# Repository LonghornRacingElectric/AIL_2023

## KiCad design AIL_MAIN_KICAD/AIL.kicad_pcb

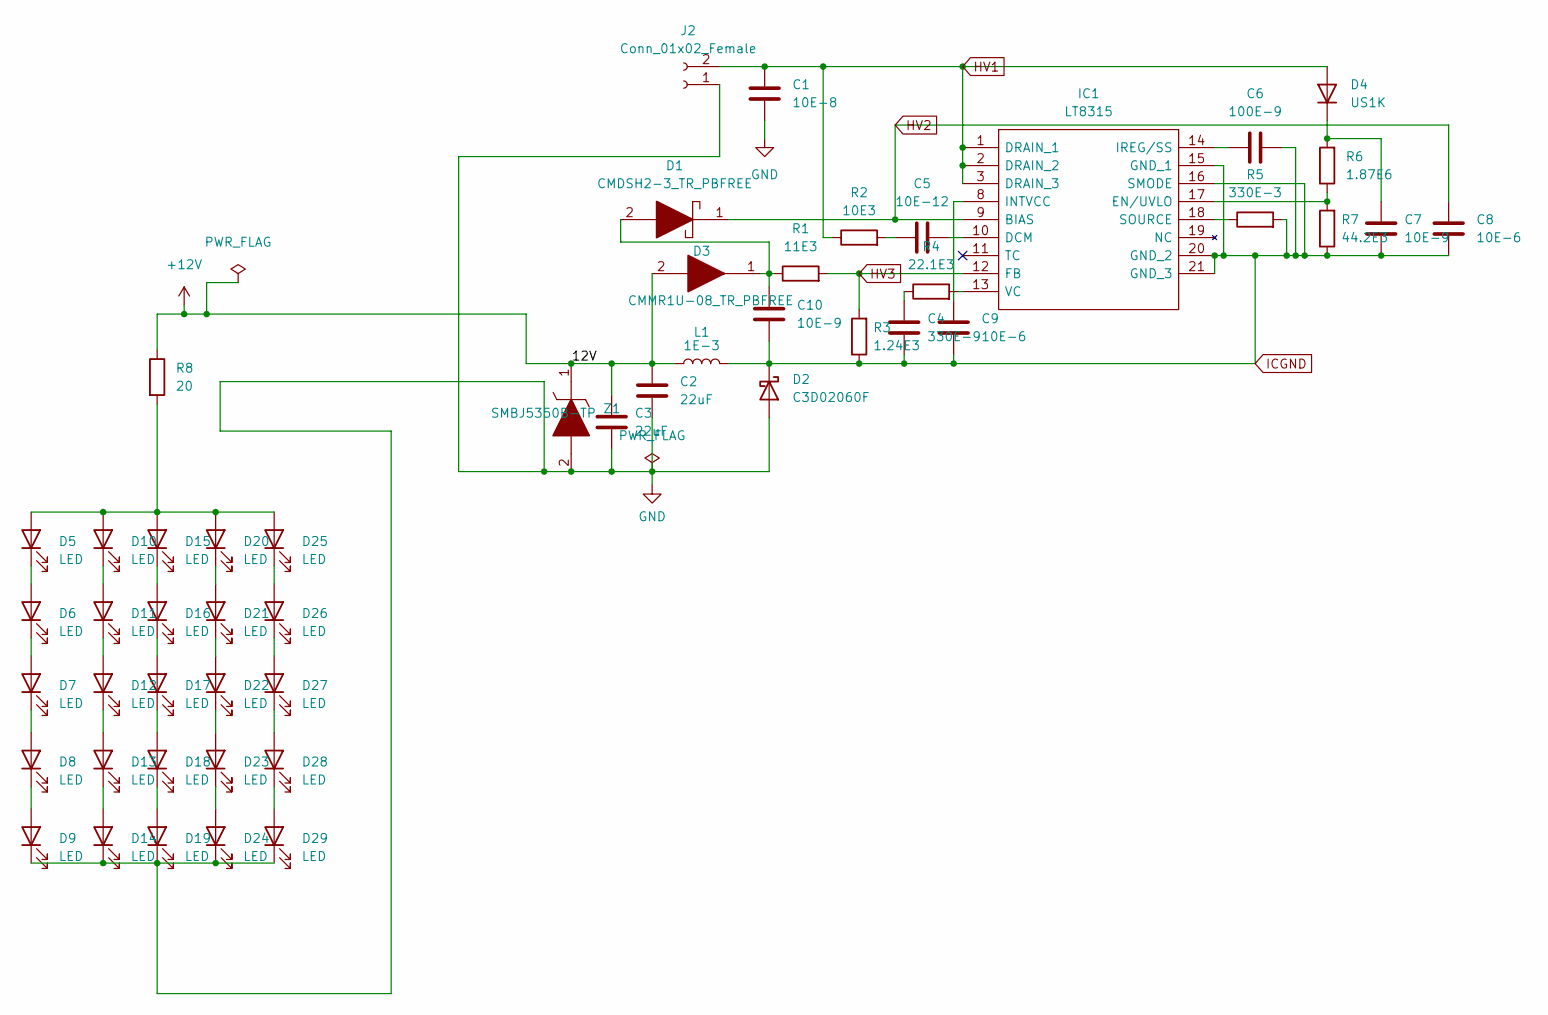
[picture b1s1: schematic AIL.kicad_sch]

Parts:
C1: 10E-8; C_1812_4532Metric_Pad1.57x3.40mm_HandSolder
C2, C3: 22uF; C_0805_2012Metric_Pad1.18x1.45mm_HandSolder
C4: 330E-9; C_01005_0402Metric_Pad0.57x0.30mm_HandSolder
C5: 10E-12; C_0603_1608Metric_Pad1.08x0.95mm_HandSolder
C6: 100E-9; C_0603_1608Metric_Pad1.08x0.95mm_HandSolder
C7, C10: 10E-9; C_0603_1608Metric_Pad1.08x0.95mm_HandSolder
C8, C9: 10E-6; C_0603_1608Metric_Pad1.08x0.95mm_HandSolder
D1: CMDSH2-3_TR_PBFREE; SOD2512X110N; Mouser Part Number 610-CMDSH2-3
D2: C3D02060F; TO508P493X1003X2057-2P
D3: CMMR1U-08_TR_PBFREE; SODFL3818X108N; Mouser Part Number 610-CMMR1U-08TR
D4: US1K; D_SMA
D5, D6, D7, D8, D9, D10, D11, D12, D13, D14, D15, D16, D17, D18, D19, D20, D21, D22, D23, D24, D25, D26, D27, D28, D29: LED; LEDC2012X100N
IC1: LT8315; FE-20-LEAD-PLASTIC-TSSOP; Manufacturer_Part_Number LT8315
J2: Conn_01x02_Female; Molex_Micro-Fit_3.0_43045-0200_2x01_P3.00mm_Horizontal
L1: 1E-3; L_Bourns_SRR1260
R1: 11E3; R_0603_1608Metric_Pad0.98x0.95mm_HandSolder
R2: 10E3; R_1206_3216Metric_Pad1.30x1.75mm_HandSolder
R3: 1.24E3; R_0603_1608Metric_Pad0.98x0.95mm_HandSolder
R4: 22.1E3; R_0603_1608Metric_Pad0.98x0.95mm_HandSolder
R5: 330E-3; R_2512_6332Metric_Pad1.40x3.35mm_HandSolder
R6: 1.87E6; C_1206_3216Metric_Pad1.33x1.80mm_HandSolder
R7: 44.2E3; R_0603_1608Metric_Pad0.98x0.95mm_HandSolder
R8: 20; R_0603_1608Metric_Pad0.98x0.95mm_HandSolder
Z1: SMBJ5350B-TP; DIOM5336X261N; Mouser Part Number 833-SMBJ5350B-TP

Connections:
+12V: C2.1, C3.1, D3.2, L1.1, R8.1, Z1.1
GND: C1.2, C2.2, C3.2, D2.2 (A), D9.1 (K), D14.1 (K), D19.1 (K), D24.1 (K), D29.1 (K), J2.1, Z1.2
HV1: C1.1, D4.2 (A), IC1.1 (DRAIN_1), IC1.2 (DRAIN_2), IC1.3 (DRAIN_3), J2.2, R2.1
HV2: C8.1, D1.1, IC1.9 (BIAS)
HV3: IC1.12 (FB), R1.2, R3.2
ICGND: C4.2, C6.2, C7.2, C8.2, C9.2, C10.2, D2.1 (K), IC1.15 (GND_1), IC1.16 (SMODE), IC1.20 (GND_2), IC1.21 (GND_3), L1.2, R3.1, R5.2, R7.1
unnamed: C4.1, R4.1
unnamed: C5.1, R2.2
unnamed: C5.2, IC1.10 (DCM)
unnamed: C6.1, IC1.14 (IREG/SS)
unnamed: C7.1, D4.1 (K), R6.2
unnamed: C9.1, IC1.8 (INTVCC)
unnamed: C10.1, D1.2, D3.1, R1.1
unnamed: D5.1 (K), D6.2 (A)
unnamed: D6.1 (K), D7.2 (A)
unnamed: D7.1 (K), D8.2 (A)
unnamed: D8.1 (K), D9.2 (A)
unnamed: D10.1 (K), D11.2 (A)
unnamed: D5.2 (A), D10.2 (A), D15.2 (A), D20.2 (A), D25.2 (A), R8.2
unnamed: D11.1 (K), D12.2 (A)
unnamed: D12.1 (K), D13.2 (A)
unnamed: D13.1 (K), D14.2 (A)
unnamed: D15.1 (K), D16.2 (A)
unnamed: D16.1 (K), D17.2 (A)
unnamed: D17.1 (K), D18.2 (A)
unnamed: D18.1 (K), D19.2 (A)
unnamed: D20.1 (K), D21.2 (A)
unnamed: D21.1 (K), D22.2 (A)
unnamed: D22.1 (K), D23.2 (A)
unnamed: D23.1 (K), D24.2 (A)
unnamed: D25.1 (K), D26.2 (A)
unnamed: D26.1 (K), D27.2 (A)
unnamed: D27.1 (K), D28.2 (A)
unnamed: D28.1 (K), D29.2 (A)
unnamed: IC1.13 (VC), R4.2
unnamed: IC1.17 (EN/UVLO), R6.1, R7.2
unnamed: IC1.18 (SOURCE), R5.1

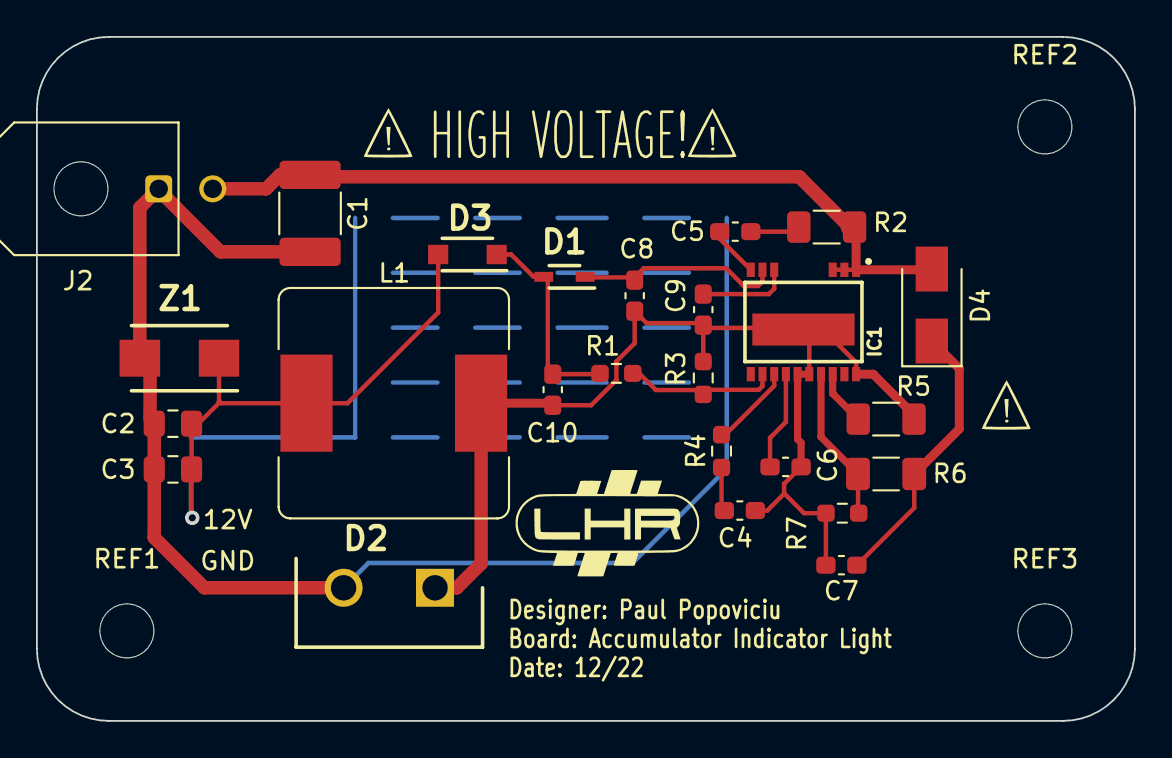
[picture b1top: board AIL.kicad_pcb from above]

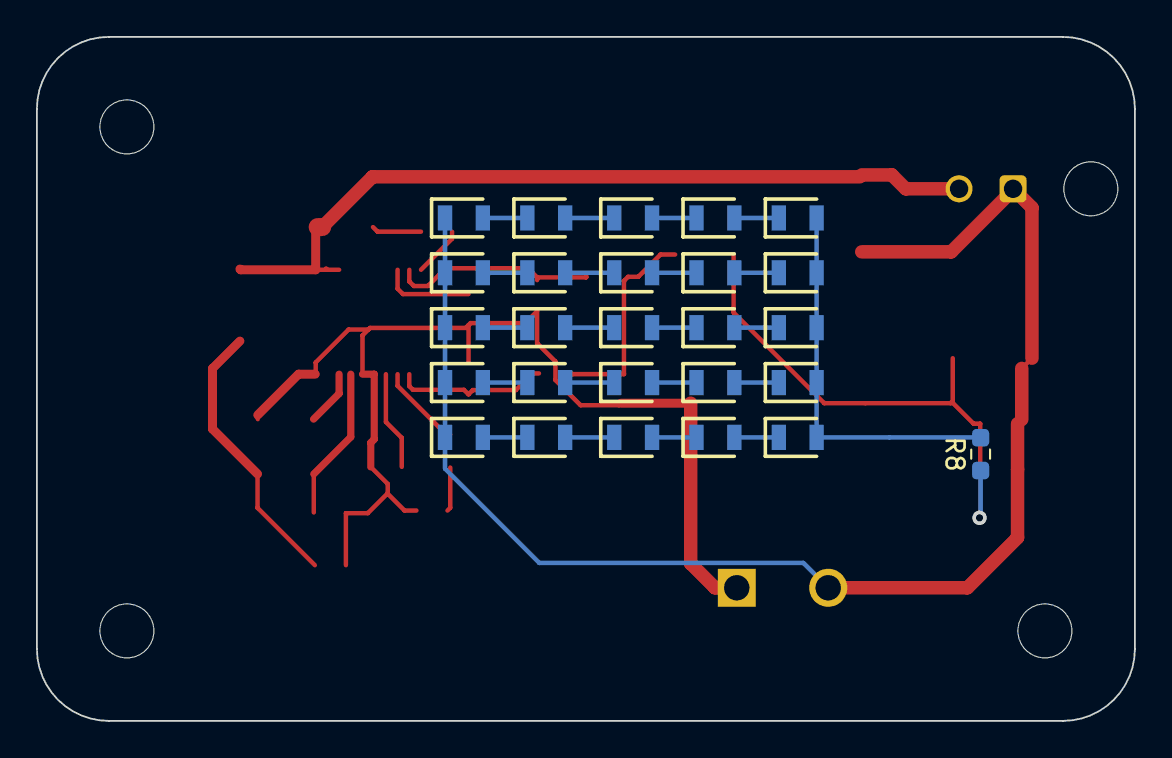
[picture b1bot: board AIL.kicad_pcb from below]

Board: 2 copper layers, 61.0 x 38.0 mm, 54 parts (26 on the bottom side), 37 nets.

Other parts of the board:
REF1, REF2, REF3: MountingHole_3mm

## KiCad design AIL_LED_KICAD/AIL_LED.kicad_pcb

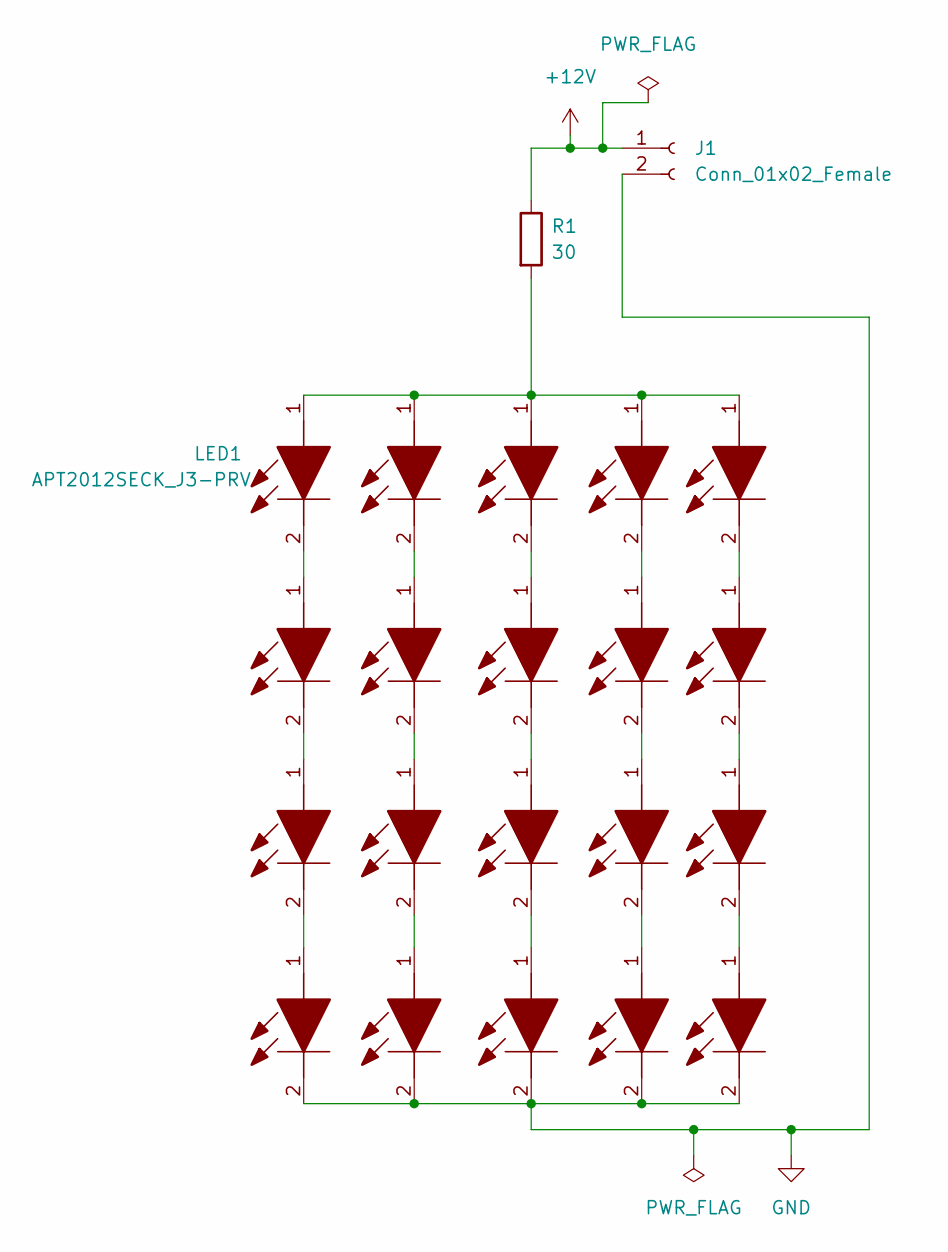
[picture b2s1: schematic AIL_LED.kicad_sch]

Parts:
J1: Conn_01x02_Female; Molex_Micro-Fit_3.0_43045-0200_2x01_P3.00mm_Horizontal
LED1, LED2, LED3, LED4, LED5, LED6, LED7, LED8, LED9, LED10, LED11, LED12, LED13, LED14, LED15, LED16, LED17, LED18, LED19, LED20: APT2012SECK_J3-PRV; APT2012SECKJ3PRV; Mouser Part Number 604-APT2012SECKJ3PRV
R1: 30; R_0603_1608Metric_Pad0.98x0.95mm_HandSolder

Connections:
+12V: J1.1, R1.1
GND: J1.2, LED4.2, LED8.2, LED12.2, LED16.2, LED20.2
unnamed: LED1.1, LED5.1, LED9.1, LED13.1, LED17.1, R1.2
unnamed: LED1.2, LED2.1
unnamed: LED2.2, LED3.1
unnamed: LED3.2, LED4.1
unnamed: LED5.2, LED6.1
unnamed: LED6.2, LED7.1
unnamed: LED7.2, LED8.1
unnamed: LED9.2, LED10.1
unnamed: LED10.2, LED11.1
unnamed: LED11.2, LED12.1
unnamed: LED13.2, LED14.1
unnamed: LED14.2, LED15.1
unnamed: LED15.2, LED16.1
unnamed: LED17.2, LED18.1
unnamed: LED18.2, LED19.1
unnamed: LED19.2, LED20.1

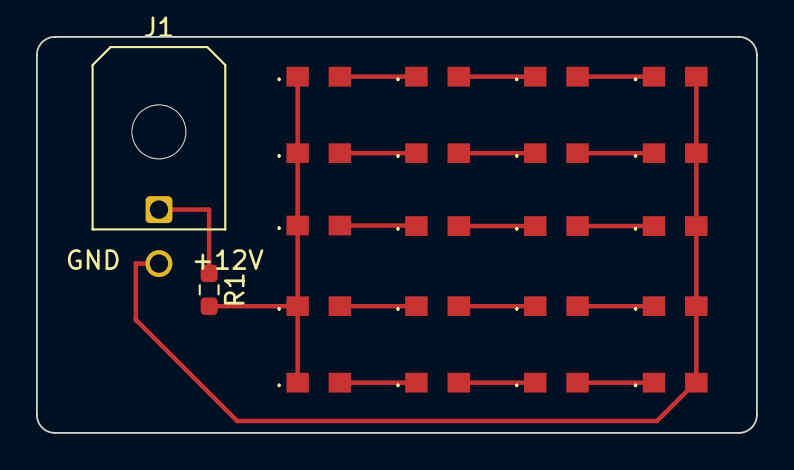
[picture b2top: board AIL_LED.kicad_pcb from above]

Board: 2 copper layers, 40.0 x 22.0 mm, 22 parts (0 on the bottom side), 18 nets.

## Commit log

2022-09-26 Added 2023KicadLibrary
2022-11-06 updating commit
2022-11-06 updating commuts
2022-11-26 Updating main board
2022-12-05 updating with BOM
2022-12-13 updating PCB with seperated BOMs
2022-12-22 Final Update to PCB
2022-12-28 updating PCB with some logos
2022-12-28 adding gerber and drill files
2022-12-28 increasing size of high current paths
2023-01-05 Fixed component BOMs for ordering
